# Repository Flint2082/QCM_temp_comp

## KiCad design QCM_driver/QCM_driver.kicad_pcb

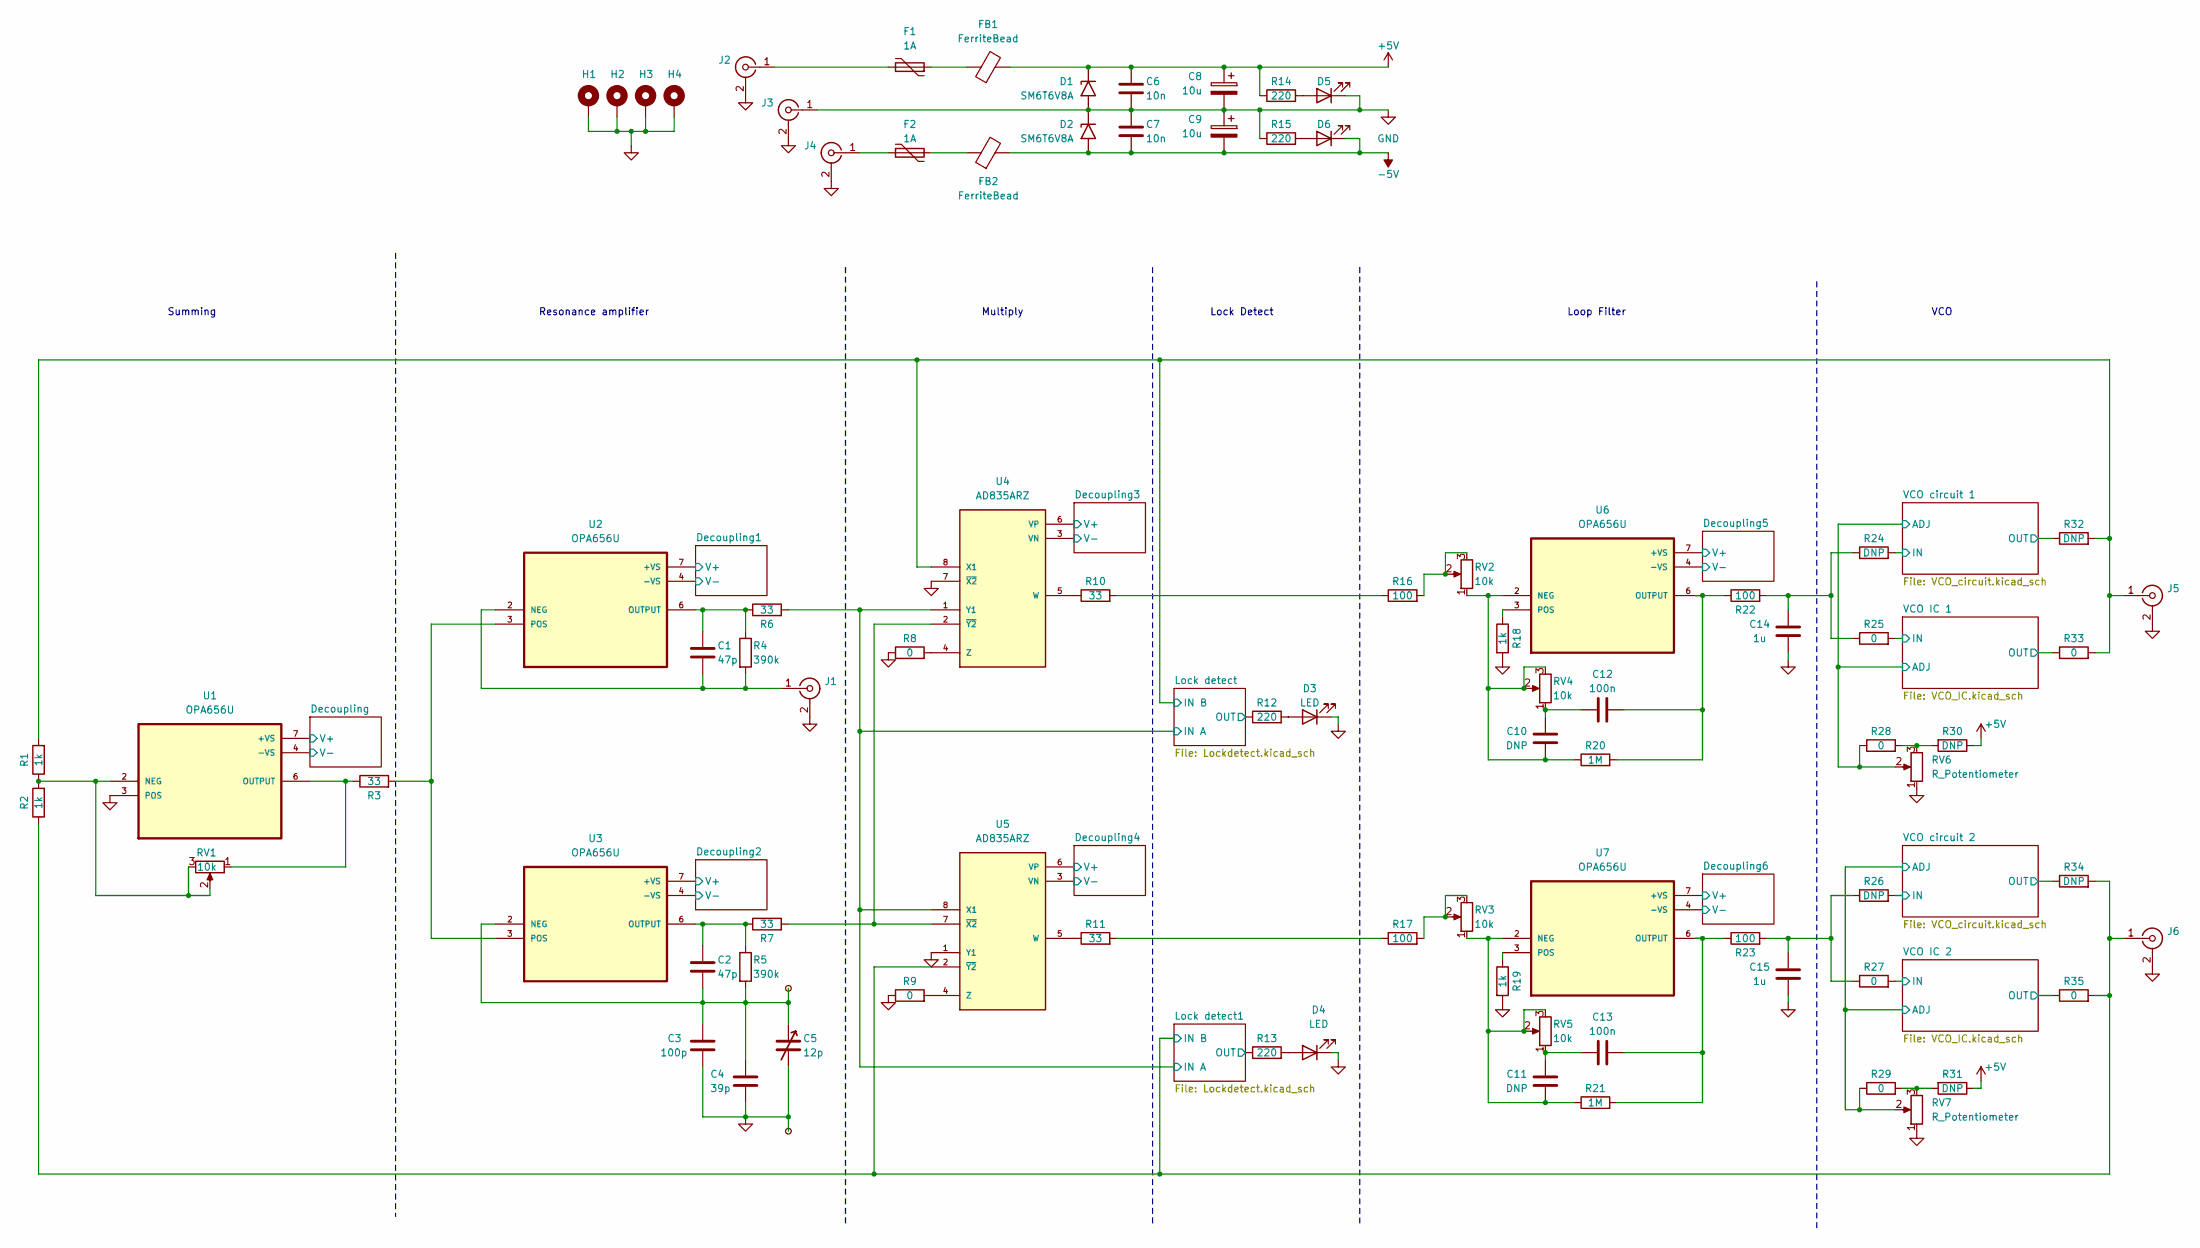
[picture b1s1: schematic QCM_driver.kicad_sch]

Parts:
C1, C2: 47p; C_1206_3216Metric
C3: 100p; C_1206_3216Metric
C4: 39p; C_1206_3216Metric
C5: 12p; Trimmer Cap 6mm
C6, C7: 10n; C_1206_3216Metric
C8, C9: 10u; CP_Elec_8x11.9
C10, C11: DNP; C_1206_3216Metric
C12, C13: 100n; C_1206_3216Metric
C14, C15: 1u; C_1210_3225Metric
D1, D2: SM6T6V8A; D_2114_3652Metric_Pad1.85x3.75mm_HandSolder
D3, D4, D5, D6: LED; LED_D5.0mm_Clear
F1, F2: 1A; Fuse_2920_7451Metric_Pad2.10x5.45mm_HandSolder
FB1, FB2: FerriteBead; C_2220_5750Metric_Pad1.97x5.40mm_HandSolder
H1, H2, H3, H4: MountingHole_Pad; MountingHole_3.2mm_M3_DIN965_Pad_TopBottom
J1, J5, J6: Conn_Coaxial; SAMTEC_BNC5-J-P-GN-RA-BH2D
J2, J3, J4: Conn_Coaxial; S16N-PC
R1, R2, R18, R19: 1k; R_1206_3216Metric_Pad1.30x1.75mm_HandSolder
R3, R6, R7, R10, R11: 33; R_1206_3216Metric_Pad1.30x1.75mm_HandSolder
R4, R5: 390k; R_1206_3216Metric_Pad1.30x1.75mm_HandSolder
R8, R9, R25, R27, R28, R29, R33, R35: 0; R_1206_3216Metric_Pad1.30x1.75mm_HandSolder
R12, R13, R14, R15: 220; R_1206_3216Metric_Pad1.30x1.75mm_HandSolder
R16, R17, R22, R23: 100; R_1206_3216Metric_Pad1.30x1.75mm_HandSolder
R20, R21: 1M; R_1206_3216Metric_Pad1.30x1.75mm_HandSolder
R24, R26, R30, R31, R32, R34: DNP; R_1206_3216Metric_Pad1.30x1.75mm_HandSolder
RV1, RV2, RV3, RV4, RV5: 10k; Potentiometer_Bourns_3296Y_Vertical
RV6, RV7: R_Potentiometer; TRIM_3590S-2-103L
TP1, TP2: TestPoint_Small; TestPoint_Pad_2.0x2.0mm
U1, U2, U3, U6, U7: OPA656U; SOIC-8_3.9x4.9mm_P1.27mm
U4, U5: AD835ARZ; SOIC-8_3.9x4.9mm_P1.27mm; PARTREV E

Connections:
+5V: C6.1, C8.1, D1.1 (A1), FB1.2, R14.1, R30.1, R31.1; also elsewhere on the board
-5V: C7.2, C9.2, D2.2 (A2), D6.1 (K), FB2.2; also elsewhere on the board
/Decoupling1/V+: U2.7 (+VS); also elsewhere on the board
/Decoupling1/V-: U2.4 (-VS); also elsewhere on the board
/Decoupling2/V+: U3.7 (+VS); also elsewhere on the board
/Decoupling2/V-: U3.4 (-VS); also elsewhere on the board
/Decoupling3/V+: U4.6 (VP); also elsewhere on the board
/Decoupling3/V-: U4.3 (VN); also elsewhere on the board
/Decoupling4/V+: U5.6 (VP); also elsewhere on the board
/Decoupling4/V-: U5.3 (VN); also elsewhere on the board
/Decoupling5/V+: U6.7 (+VS); also elsewhere on the board
/Decoupling5/V-: U6.4 (-VS); also elsewhere on the board
/Decoupling6/V+: U7.7 (+VS); also elsewhere on the board
/Decoupling6/V-: U7.4 (-VS); also elsewhere on the board
/Decoupling/V+: U1.7 (+VS); also elsewhere on the board
/Decoupling/V-: U1.4 (-VS); also elsewhere on the board
/Lock detect1/IN B: J6.1 (In), R2.1, R34.2, R35.2, U5.2 (~Y2); also elsewhere on the board
/Lock detect1/OUT: R13.1; also elsewhere on the board
/Lock detect/IN A: R6.2, U4.1 (Y1), U5.8 (X1); also elsewhere on the board
/Lock detect/IN B: J5.1 (In), R1.2, R32.2, R33.2, U4.8 (X1); also elsewhere on the board
/Lock detect/OUT: R12.1; also elsewhere on the board
/VCO IC B 1/ADJ: R28.1, RV6.2; also elsewhere on the board
/VCO IC B 1/IN: R25.2; also elsewhere on the board
/VCO IC B 1/OUT: R33.1; also elsewhere on the board
/VCO IC B 2/ADJ: R29.1, RV7.2; also elsewhere on the board
/VCO IC B 2/IN: R27.2; also elsewhere on the board
/VCO IC B 2/OUT: R35.1; also elsewhere on the board
/VCO circuit 1/IN: R24.2; also elsewhere on the board
/VCO circuit 1/OUT: R32.1; also elsewhere on the board
/VCO circuit 2/IN: R26.2; also elsewhere on the board
/VCO circuit 2/OUT: R34.1; also elsewhere on the board
GND: C3.2, C4.2, C5.2, C6.2, C7.1, C8.2, C9.1, C14.1, C15.1, D1.2 (A2), D2.1 (A1), D3.1 (K), D4.1 (K), D5.1 (K), H1.1, H2.1, H3.1, H4.1, J1.2 (Ext), J2.2 (Ext), J3.1 (In), J3.2 (Ext), J4.2 (Ext), J5.2 (Ext), J6.2 (Ext), R8.1, R9.1, R15.1, R18.2, R19.2, RV6.1, RV7.1, TP2.1, U1.3 (POS), U4.7 (~X2), U5.1 (Y1); also elsewhere on the board
unnamed: C10.2, C12.1, RV4.1
unnamed: C11.2, C13.1, RV5.1
unnamed: C14.2, R22.2, R24.1, R25.1
unnamed: C15.2, R23.2, R26.1, R27.1
unnamed: D3.2 (A), R12.2
unnamed: D4.2 (A), R13.2
unnamed: D5.2 (A), R14.2
unnamed: D6.2 (A), R15.2
unnamed: F1.1, FB1.1
unnamed: F2.2, FB2.1
unnamed: C1.2, J1.1 (In), R4.2, U2.2 (NEG)
unnamed: F1.2, J2.1 (In)
unnamed: F2.1, J4.1 (In)
unnamed: R10.2, R16.1
unnamed: R11.2, R17.1
unnamed: R16.2, RV2.2, RV2.3
unnamed: R17.2, RV3.2, RV3.3
unnamed: R28.2, R30.2, RV6.3
unnamed: R29.2, R31.2, RV7.3
unnamed: R1.1, R2.2, RV1.2, RV1.3, U1.2 (NEG)
unnamed: R3.1, RV1.1, U1.6 (OUTPUT)
unnamed: C1.1, R4.1, R6.1, U2.6 (OUTPUT)
unnamed: R3.2, U2.3 (POS), U3.3 (POS)
unnamed: C2.2, C3.1, C4.1, C5.1, R5.2, TP1.1, U3.2 (NEG)
unnamed: C2.1, R5.1, R7.1, U3.6 (OUTPUT)
unnamed: R10.1, U4.5 (W)
unnamed: R8.2, U4.4 (Z)
unnamed: R7.2, U4.2 (~Y2), U5.7 (~X2)
unnamed: R11.1, U5.5 (W)
unnamed: R9.2, U5.4 (Z)
unnamed: C10.1, R20.1, RV2.1, RV4.2, RV4.3, U6.2 (NEG)
unnamed: C12.2, R20.2, R22.1, U6.6 (OUTPUT)
unnamed: R18.1, U6.3 (POS)
unnamed: C11.1, R21.1, RV3.1, RV5.2, RV5.3, U7.2 (NEG)
unnamed: C13.2, R21.2, R23.1, U7.6 (OUTPUT)
unnamed: R19.1, U7.3 (POS)

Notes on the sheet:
VCO
Loop Filter
Multiply
Summing
Lock Detect
Resonance amplifier

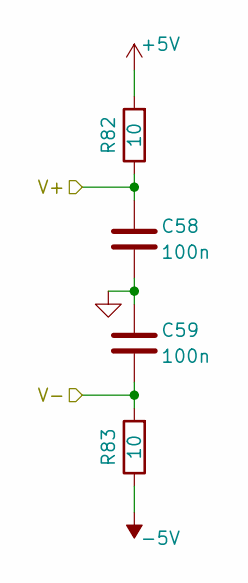
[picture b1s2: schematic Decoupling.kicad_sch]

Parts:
C58, C59: 100n; C_1206_3216Metric
R82, R83: 10; R_1206_3216Metric_Pad1.30x1.75mm_HandSolder

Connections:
+5V: R82.2; also elsewhere on the board
-5V: R83.1; also elsewhere on the board
/Decoupling/V+: C58.1, R82.1; also elsewhere on the board
/Decoupling/V-: C59.2, R83.2; also elsewhere on the board
GND: C58.2, C59.1; also elsewhere on the board

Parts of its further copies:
C16, C17, C18, C19, C72, C73, C74, C75, C76, C77, C78, C79: 100n; C_1206_3216Metric
R36, R37, R38, R39, R100, R101, R102, R103, R104, R105, R106, R107: 10; R_1206_3216Metric_Pad1.30x1.75mm_HandSolder

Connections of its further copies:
+5V: R36.2, R38.2, R100.2, R102.2, R104.2, R106.2; also elsewhere on the board
-5V: R37.1, R39.1, R101.1, R103.1, R105.1, R107.1; also elsewhere on the board
/Decoupling1/V+: C16.1, R36.1; also elsewhere on the board
/Decoupling1/V-: C17.2, R37.2; also elsewhere on the board
/Decoupling2/V+: C18.1, R38.1; also elsewhere on the board
/Decoupling2/V-: C19.2, R39.2; also elsewhere on the board
/Decoupling3/V+: C72.1, R100.1; also elsewhere on the board
/Decoupling3/V-: C73.2, R101.2; also elsewhere on the board
/Decoupling4/V+: C74.1, R102.1; also elsewhere on the board
/Decoupling4/V-: C75.2, R103.2; also elsewhere on the board
/Decoupling5/V+: C76.1, R104.1; also elsewhere on the board
/Decoupling5/V-: C77.2, R105.2; also elsewhere on the board
/Decoupling6/V+: C78.1, R106.1; also elsewhere on the board
/Decoupling6/V-: C79.2, R107.2; also elsewhere on the board
GND: C16.2, C17.1, C18.2, C19.1, C72.2, C73.1, C74.2, C75.1, C76.2, C77.1, C78.2, C79.1; also elsewhere on the board

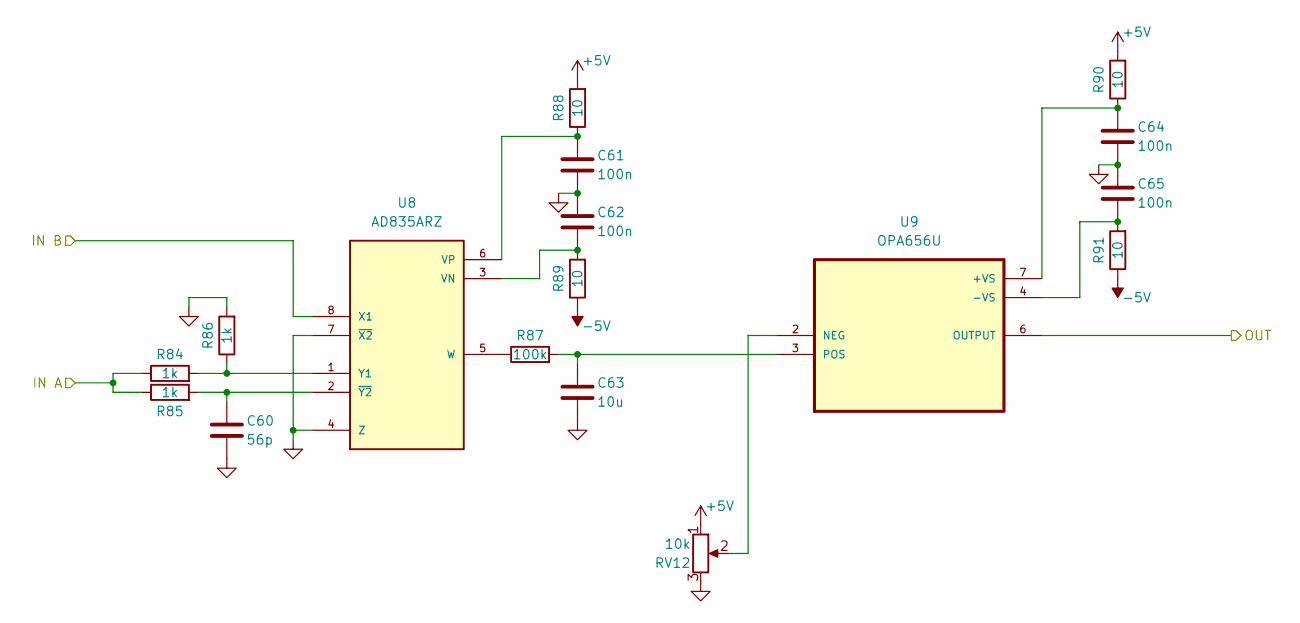
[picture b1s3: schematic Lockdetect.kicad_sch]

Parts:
C60: 56p; C_1206_3216Metric
C61, C62, C64, C65: 100n; C_1206_3216Metric
C63: 10u; C_1210_3225Metric
R84, R85, R86: 1k; R_1206_3216Metric_Pad1.30x1.75mm_HandSolder
R87: 100k; R_1206_3216Metric_Pad1.30x1.75mm_HandSolder
R88, R89, R90, R91: 10; R_1206_3216Metric_Pad1.30x1.75mm_HandSolder
RV12: 10k; Potentiometer_Bourns_3296Y_Vertical
U8: AD835ARZ; SOIC-8_3.9x4.9mm_P1.27mm; PARTREV E
U9: OPA656U; SOIC-8_3.9x4.9mm_P1.27mm

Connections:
+5V: R88.2, R90.2, RV12.1; also elsewhere on the board
-5V: R89.1, R91.1; also elsewhere on the board
/Lock detect/IN A: R84.1, R85.1; also elsewhere on the board
/Lock detect/IN B: U8.8 (X1); also elsewhere on the board
/Lock detect/OUT: U9.6 (OUTPUT); also elsewhere on the board
GND: C60.2, C61.2, C62.1, C63.2, C64.2, C65.1, R86.2, RV12.3, U8.4 (Z), U8.7 (~X2); also elsewhere on the board
unnamed: C62.2, R89.2, U8.3 (VN)
unnamed: C61.1, R88.1, U8.6 (VP)
unnamed: R87.1, U8.5 (W)
unnamed: R84.2, R86.1, U8.1 (Y1)
unnamed: C60.1, R85.2, U8.2 (~Y2)
unnamed: C64.1, R90.1, U9.7 (+VS)
unnamed: C65.2, R91.2, U9.4 (-VS)
unnamed: RV12.2, U9.2 (NEG)
unnamed: C63.1, R87.2, U9.3 (POS)

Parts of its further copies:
C66: 56p; C_1206_3216Metric
C67, C68, C70, C71: 100n; C_1206_3216Metric
C69: 10u; C_1210_3225Metric
R92, R93, R94: 1k; R_1206_3216Metric_Pad1.30x1.75mm_HandSolder
R95: 100k; R_1206_3216Metric_Pad1.30x1.75mm_HandSolder
R96, R97, R98, R99: 10; R_1206_3216Metric_Pad1.30x1.75mm_HandSolder
RV13: 10k; Potentiometer_Bourns_3296Y_Vertical
U10: AD835ARZ; SOIC-8_3.9x4.9mm_P1.27mm; PARTREV E
U11: OPA656U; SOIC-8_3.9x4.9mm_P1.27mm

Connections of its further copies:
+5V: R96.2, R98.2, RV13.1; also elsewhere on the board
-5V: R97.1, R99.1; also elsewhere on the board
/Lock detect1/IN B: U10.8 (X1); also elsewhere on the board
/Lock detect1/OUT: U11.6 (OUTPUT); also elsewhere on the board
/Lock detect/IN A: R92.1, R93.1; also elsewhere on the board
GND: C66.2, C67.2, C68.1, C69.2, C70.2, C71.1, R94.2, RV13.3, U10.4 (Z), U10.7 (~X2); also elsewhere on the board
unnamed: C68.2, R97.2, U10.3 (VN)
unnamed: C67.1, R96.1, U10.6 (VP)
unnamed: R95.1, U10.5 (W)
unnamed: R92.2, R94.1, U10.1 (Y1)
unnamed: C66.1, R93.2, U10.2 (~Y2)
unnamed: C70.1, R98.1, U11.7 (+VS)
unnamed: C71.2, R99.2, U11.4 (-VS)
unnamed: RV13.2, U11.2 (NEG)
unnamed: C69.1, R95.2, U11.3 (POS)

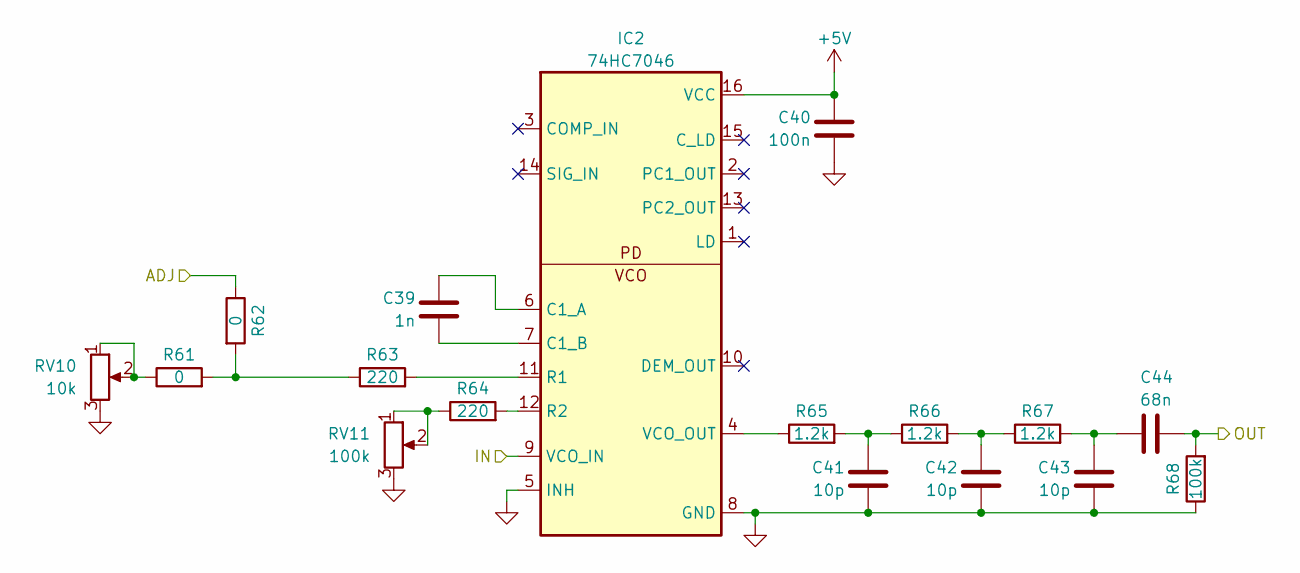
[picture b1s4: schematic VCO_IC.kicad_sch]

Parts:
C39: 1n; C_1206_3216Metric
C40: 100n; C_1206_3216Metric
C41, C42, C43: 10p; C_1206_3216Metric
C44: 68n; C_1206_3216Metric
IC2: 74HC7046; SOIC-16_3.9x9.9mm_P1.27mm
R61, R62: 0; R_1206_3216Metric_Pad1.30x1.75mm_HandSolder
R63, R64: 220; R_1206_3216Metric_Pad1.30x1.75mm_HandSolder
R65, R66, R67: 1.2k; R_1206_3216Metric_Pad1.30x1.75mm_HandSolder
R68: 100k; R_1206_3216Metric_Pad1.30x1.75mm_HandSolder
RV10: 10k; Potentiometer_Bourns_3296Y_Vertical
RV11: 100k; Potentiometer_Bourns_3296Y_Vertical

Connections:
+5V: C40.2, IC2.16 (VCC); also elsewhere on the board
/VCO IC B 2/ADJ: R62.1; also elsewhere on the board
/VCO IC B 2/IN: IC2.9 (VCO_IN); also elsewhere on the board
/VCO IC B 2/OUT: C44.1, R68.2; also elsewhere on the board
GND: C40.1, C41.1, C42.1, C43.1, IC2.5 (INH), IC2.8 (GND), R68.1, RV10.3, RV11.3; also elsewhere on the board
unnamed: C41.2, R65.2, R66.1
unnamed: C42.2, R66.2, R67.1
unnamed: C43.2, C44.2, R67.2
unnamed: C39.2, IC2.6 (C1_A)
unnamed: C39.1, IC2.7 (C1_B)
unnamed: IC2.11 (R1), R63.2
unnamed: IC2.12 (R2), R64.2
unnamed: IC2.4 (VCO_OUT), R65.1
unnamed: R61.1, RV10.1, RV10.2
unnamed: R61.2, R62.2, R63.1
unnamed: R64.1, RV11.1, RV11.2

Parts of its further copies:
C33: 1n; C_1206_3216Metric
C34: 100n; C_1206_3216Metric
C35, C36, C37: 10p; C_1206_3216Metric
C38: 68n; C_1206_3216Metric
IC1: 74HC7046; SOIC-16_3.9x9.9mm_P1.27mm
R53, R54: 0; R_1206_3216Metric_Pad1.30x1.75mm_HandSolder
R55, R56: 220; R_1206_3216Metric_Pad1.30x1.75mm_HandSolder
R57, R58, R59: 1.2k; R_1206_3216Metric_Pad1.30x1.75mm_HandSolder
R60: 100k; R_1206_3216Metric_Pad1.30x1.75mm_HandSolder
RV8: 10k; Potentiometer_Bourns_3296Y_Vertical
RV9: 100k; Potentiometer_Bourns_3296Y_Vertical

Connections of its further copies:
+5V: C34.2, IC1.16 (VCC); also elsewhere on the board
/VCO IC B 1/ADJ: R54.1; also elsewhere on the board
/VCO IC B 1/IN: IC1.9 (VCO_IN); also elsewhere on the board
/VCO IC B 1/OUT: C38.1, R60.2; also elsewhere on the board
GND: C34.1, C35.1, C36.1, C37.1, IC1.5 (INH), IC1.8 (GND), R60.1, RV8.3, RV9.3; also elsewhere on the board
unnamed: C35.2, R57.2, R58.1
unnamed: C36.2, R58.2, R59.1
unnamed: C37.2, C38.2, R59.2
unnamed: C33.2, IC1.6 (C1_A)
unnamed: C33.1, IC1.7 (C1_B)
unnamed: IC1.11 (R1), R55.2
unnamed: IC1.12 (R2), R56.2
unnamed: IC1.4 (VCO_OUT), R57.1
unnamed: R53.1, RV8.1, RV8.2
unnamed: R53.2, R54.2, R55.1
unnamed: R56.1, RV9.1, RV9.2

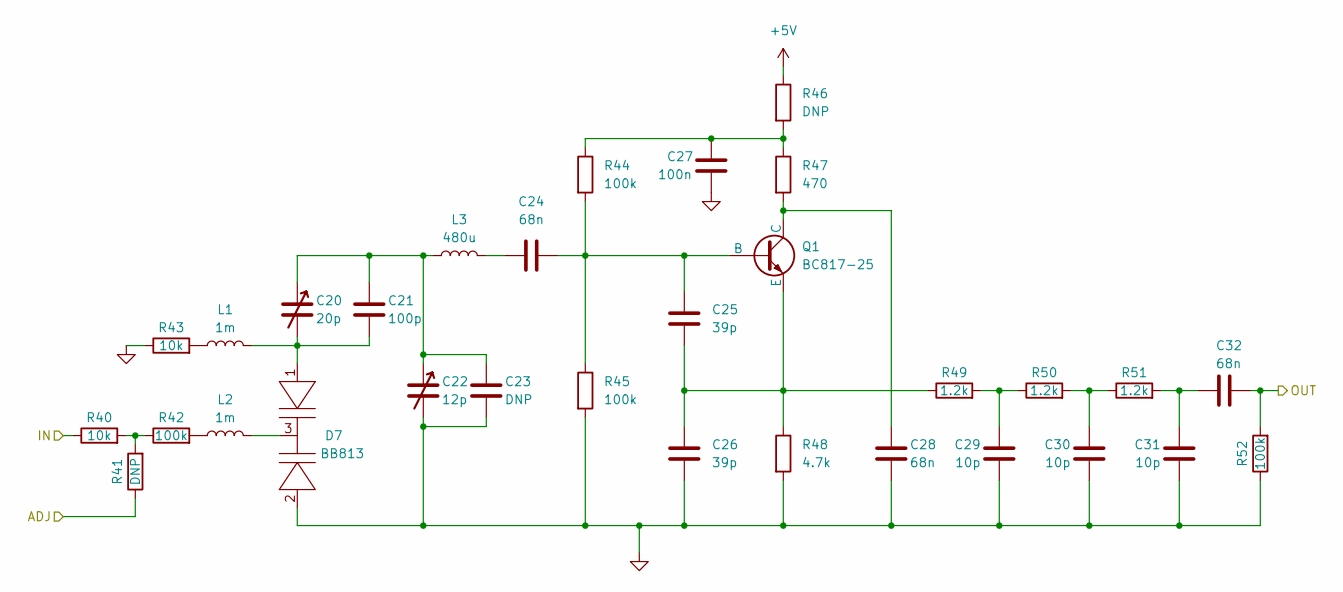
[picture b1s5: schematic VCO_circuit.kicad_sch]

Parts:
C20: 20p; Trimmer Cap 6mm
C21: 100p; C_1206_3216Metric
C22: 12p; Trimmer Cap 6mm
C23: DNP; C_1206_3216Metric
C24, C28, C32: 68n; C_1206_3216Metric
C25, C26: 39p; C_1206_3216Metric
C27: 100n; C_1206_3216Metric
C29, C30, C31: 10p; C_1206_3216Metric
D7: BB813; SOT-23
L1, L2: 1m; L_12x12mm_H8mm
L3: 480u; L_12x12mm_H8mm
Q1: BC817-25; SOT-23
R40, R43: 10k; R_1206_3216Metric_Pad1.30x1.75mm_HandSolder
R41, R46: DNP; R_1206_3216Metric_Pad1.30x1.75mm_HandSolder
R42, R44, R45, R52: 100k; R_1206_3216Metric_Pad1.30x1.75mm_HandSolder
R47: 470; R_1206_3216Metric_Pad1.30x1.75mm_HandSolder
R48: 4.7k; R_1206_3216Metric_Pad1.30x1.75mm_HandSolder
R49, R50, R51: 1.2k; R_1206_3216Metric_Pad1.30x1.75mm_HandSolder

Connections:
+5V: R46.1; also elsewhere on the board
/VCO IC B 2/ADJ: R41.1; also elsewhere on the board
/VCO circuit 2/IN: R40.1; also elsewhere on the board
/VCO circuit 2/OUT: C32.1, R52.2; also elsewhere on the board
GND: C22.2, C23.1, C26.1, C27.2, C28.1, C29.1, C30.1, C31.1, D7.2, R43.1, R45.2, R48.2, R52.1; also elsewhere on the board
unnamed: C20.1, C21.2, C22.1, C23.2, L3.1
unnamed: C20.2, C21.1, D7.1, L1.2
unnamed: C24.1, L3.2
unnamed: C27.1, R44.1, R46.2, R47.1
unnamed: C29.2, R49.2, R50.1
unnamed: C30.2, R50.2, R51.1
unnamed: C31.2, C32.2, R51.2
unnamed: D7.3, L2.2
unnamed: L1.1, R43.2
unnamed: L2.1, R42.2
unnamed: C24.2, C25.2, Q1.2 (B), R44.2, R45.1
unnamed: C28.2, Q1.1 (C), R47.2
unnamed: C25.1, C26.2, Q1.3 (E), R48.1, R49.1
unnamed: R40.2, R41.2, R42.1

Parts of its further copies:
C45: 20p; Trimmer Cap 6mm
C46: 100p; C_1206_3216Metric
C47: 12p; Trimmer Cap 6mm
C48: DNP; C_1206_3216Metric
C49, C53, C57: 68n; C_1206_3216Metric
C50, C51: 39p; C_1206_3216Metric
C52: 100n; C_1206_3216Metric
C54, C55, C56: 10p; C_1206_3216Metric
D8: BB813; SOT-23
L4, L5: 1m; L_12x12mm_H8mm
L6: 480u; L_12x12mm_H8mm
Q2: BC817-25; SOT-23
R69, R72: 10k; R_1206_3216Metric_Pad1.30x1.75mm_HandSolder
R71, R73, R74, R81: 100k; R_1206_3216Metric_Pad1.30x1.75mm_HandSolder
R76: 470; R_1206_3216Metric_Pad1.30x1.75mm_HandSolder
R77: 4.7k; R_1206_3216Metric_Pad1.30x1.75mm_HandSolder
R78, R79, R80: 1.2k; R_1206_3216Metric_Pad1.30x1.75mm_HandSolder

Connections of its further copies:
/VCO circuit 1/IN: R69.1; also elsewhere on the board
/VCO circuit 1/OUT: C57.1, R81.2; also elsewhere on the board
GND: C47.2, C48.1, C51.1, C52.2, C53.1, C54.1, C55.1, C56.1, D8.2, R72.1, R74.2, R77.2, R81.1; also elsewhere on the board
unnamed: C45.1, C46.2, C47.1, C48.2, L6.1
unnamed: C45.2, C46.1, D8.1, L4.2
unnamed: C49.1, L6.2
unnamed 52: C52.1, R73.1, R76.1; also elsewhere on the board
unnamed: C54.2, R78.2, R79.1
unnamed: C55.2, R79.2, R80.1
unnamed: C56.2, C57.2, R80.2
unnamed: D8.3, L5.2
unnamed: L4.1, R72.2
unnamed: L5.1, R71.2
unnamed: C49.2, C50.2, Q2.2 (B), R73.2, R74.1
unnamed: C53.2, Q2.1 (C), R76.2
unnamed: C50.1, C51.2, Q2.3 (E), R77.1, R78.1
unnamed 100: R69.2, R71.1; also elsewhere on the board

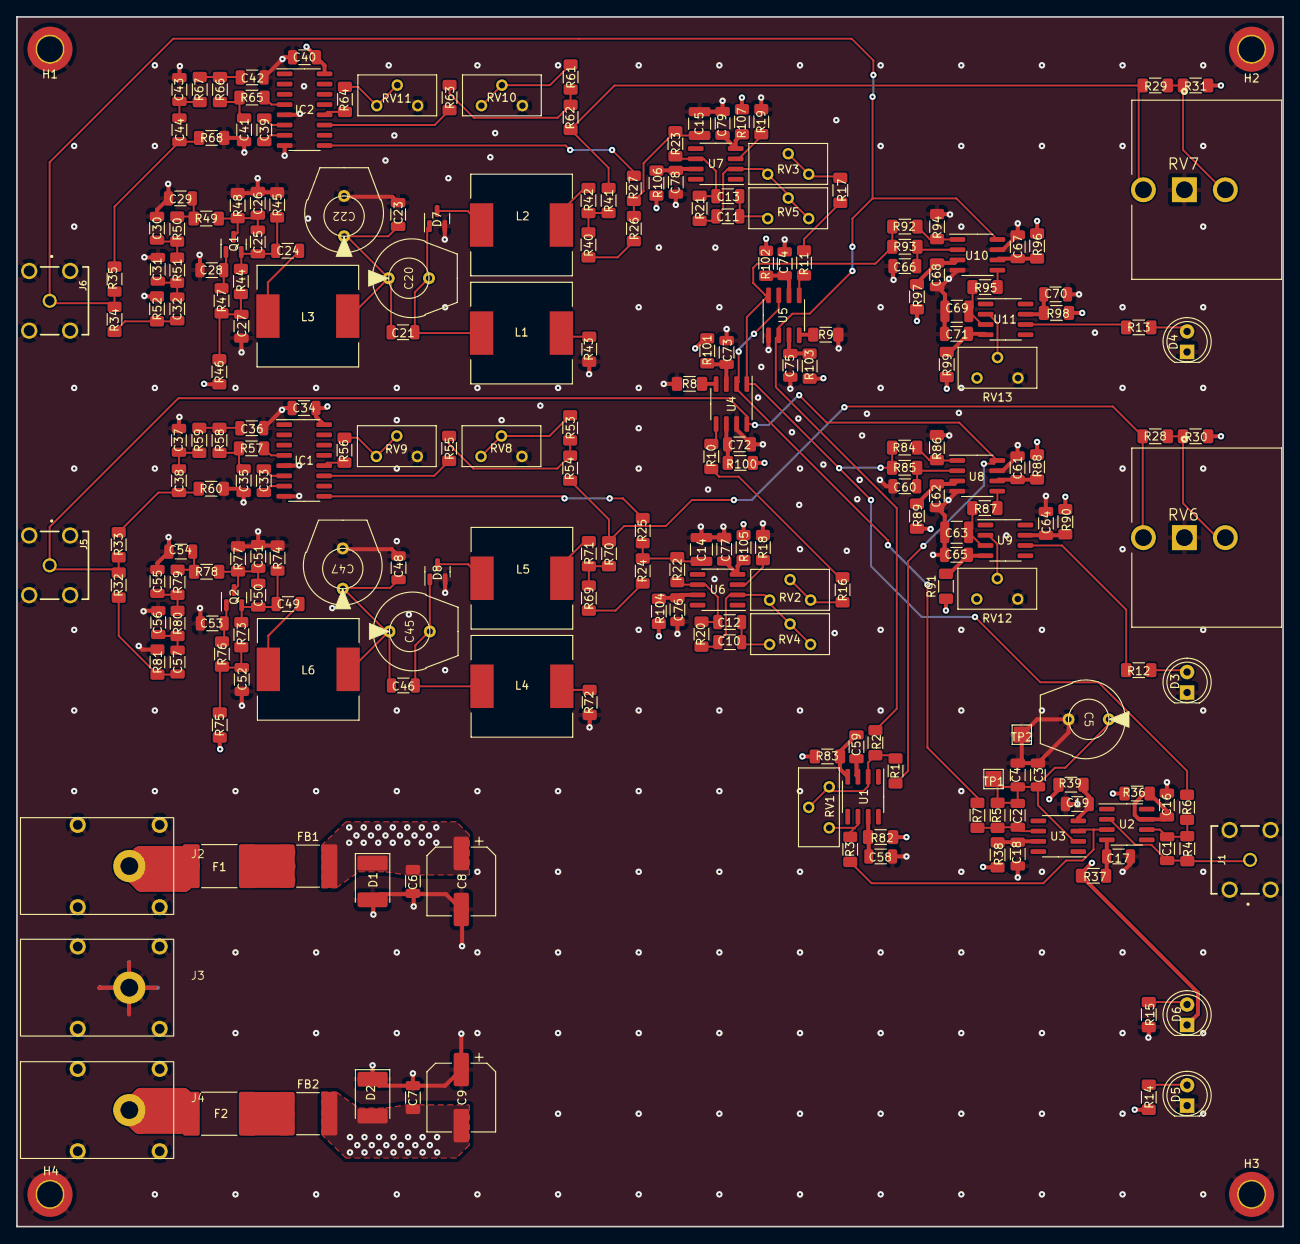
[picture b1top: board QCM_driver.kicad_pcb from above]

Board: 4 copper layers, 157.0 x 150.0 mm, 244 parts (0 on the bottom side), 136 nets.

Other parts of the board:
R70: 10k; R_1206_3216Metric_Pad1.30x1.75mm_HandSolder
R75: 0; R_1206_3216Metric_Pad1.30x1.75mm_HandSolder

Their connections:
+5V: R75.1; also elsewhere on the board
/VCO IC B 1/ADJ: R70.1; also elsewhere on the board
unnamed 52: R75.2; also elsewhere on the board
unnamed 100: R70.2; also elsewhere on the board

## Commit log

2025-06-25 PCB and schematic V1.0
2025-06-25 Organisation
2025-07-08 Script schoongemaakt
2025-07-08 Gebruikersvriendelijker gemaakt
2025-07-08 Debug Hardware aanpassingen overgezet naar KiCad
2025-07-08 Toevoeging Handleiding, Hardware aanpassing log, en kalibratie excelbestand
2025-12-24 Improved algorithem speed by 100x by replacing the symbolic sover with a numerical one. Also added the thesis text for reference
2025-12-24 moved constant stuff out of the while loop to speed up the process
